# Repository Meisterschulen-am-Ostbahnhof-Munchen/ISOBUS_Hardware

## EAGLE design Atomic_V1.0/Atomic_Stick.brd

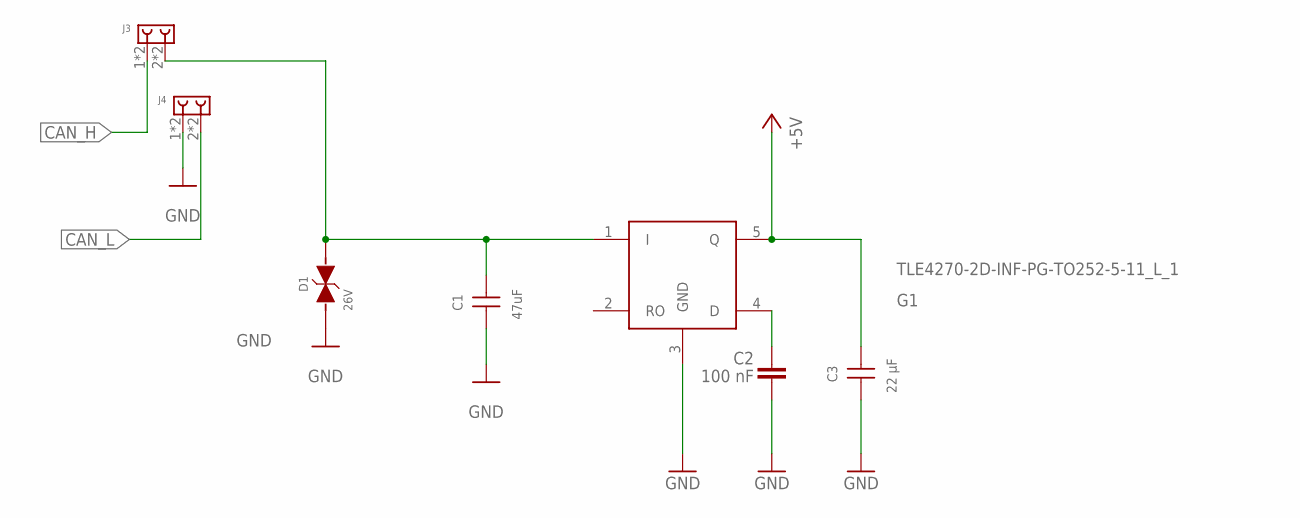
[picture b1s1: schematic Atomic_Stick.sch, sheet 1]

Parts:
C1: 47uF; WCAP-CSGP_1210_H2.5
C2: 100 nF; WCAP-CSGP_0402
C3: 22 µF; WCAP-CSGP_0805_H1.25_R
D1: 26V; WE-TVSP_DO-214AC_BIDIRECTIONAL
G1: TLE4270-2D-INF-PG-TO252-5-11_L_1; INF-PG-TO252-5-11_L_1PRIMARY
J3, J4: 695402400222

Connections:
+5V: C3.2, G1.5 (Q); also elsewhere on the board
+12V: C1.2, D1.2, G1.1 (I), J3.2, J3.A2 (2)
CAN_H: J3.1, J3.A1 (1); also elsewhere on the board
CAN_L: J4.2, J4.A2 (2); also elsewhere on the board
GND: C1.1, C2.2, C3.1, D1.1, G1.3 (GND), J4.1, J4.A1 (1); also elsewhere on the board
unnamed: C2.1, G1.4 (D)

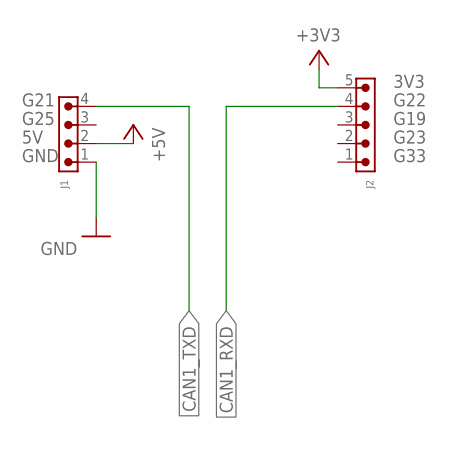
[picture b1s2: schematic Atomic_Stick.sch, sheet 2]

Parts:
J1: 6130XX11121_61300411121; 61300411121
J2: 6130XX11121_61300511121; 61300511121

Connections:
+3V3: J2.5; also elsewhere on the board
+5V: J1.2; also elsewhere on the board
CAN1_RXD: J2.4; also elsewhere on the board
CAN1_TXD: J1.4; also elsewhere on the board
GND: J1.1; also elsewhere on the board

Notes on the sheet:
GND
G25
G21
G33
G23
G19
G22
3V3

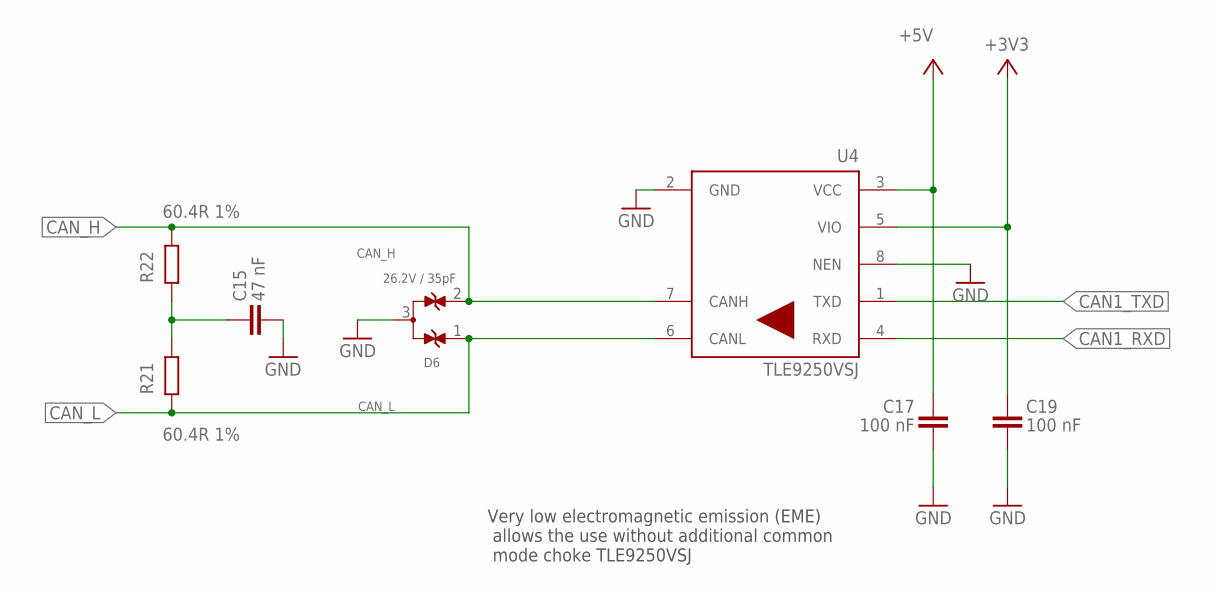
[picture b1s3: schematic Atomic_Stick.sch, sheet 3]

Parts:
C15: 47 nF; WCAP-CSGP_0402
C17, C19: 100 nF; WCAP-CSGP_0402
D6: 26.2V / 35pF; WE-TVS_SOT23-3L
R21, R22: 60.4R 1%; WCAP-CSRF_0402
U4: TLE9250VSJ; SOIC127P602X173-8N-V

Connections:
+3V3: C19.1, U4.5 (VIO); also elsewhere on the board
+5V: C17.1, U4.3 (VCC); also elsewhere on the board
CAN1_RXD: U4.4 (RXD); also elsewhere on the board
CAN1_TXD: U4.1 (TXD); also elsewhere on the board
CAN_H: D6.2, R22.2, U4.7 (CANH); also elsewhere on the board
CAN_L: D6.1, R21.1, U4.6 (CANL); also elsewhere on the board
GND: C15.2, C17.2, C19.2, D6.3, U4.2 (GND), U4.8 (NEN); also elsewhere on the board
unnamed: C15.1, R21.2, R22.1

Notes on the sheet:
Very low electromagnetic emission (EME) allows the use without additional common mode choke TLE9250VSJ

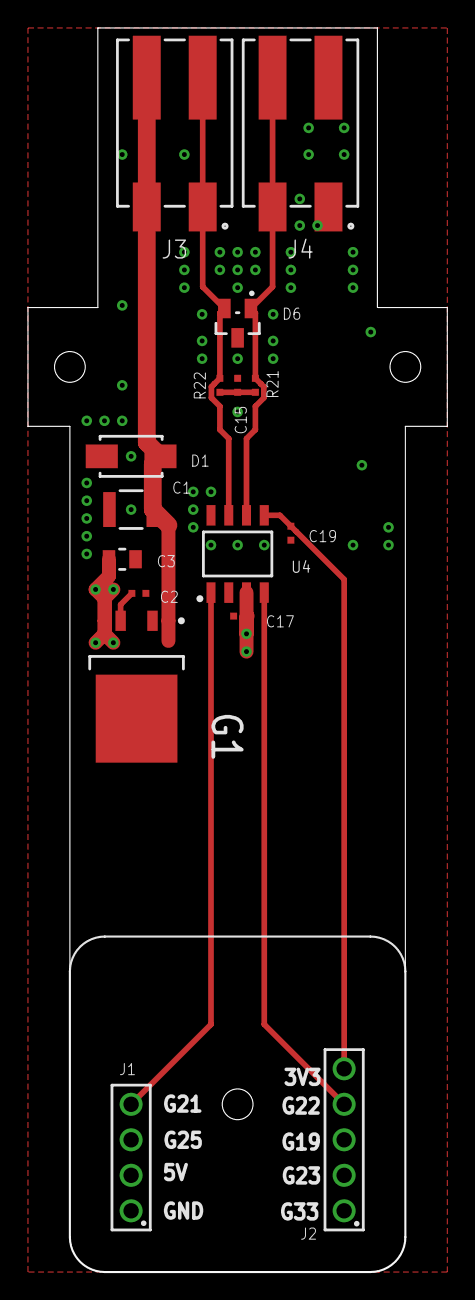
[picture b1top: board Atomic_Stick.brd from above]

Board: 2 copper layers, 30.0 x 89.0 mm, 16 parts (0 on the bottom side), 10 nets.

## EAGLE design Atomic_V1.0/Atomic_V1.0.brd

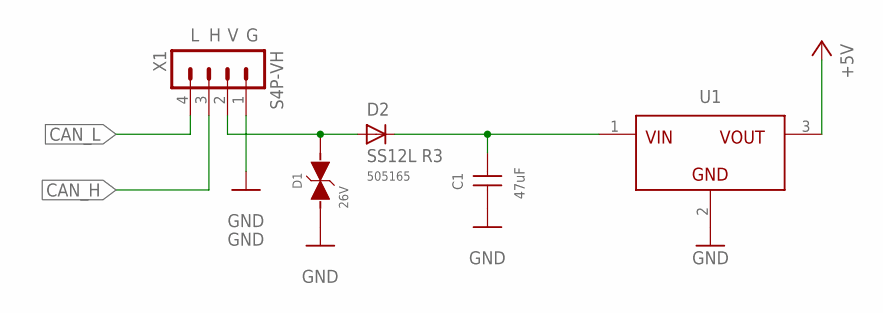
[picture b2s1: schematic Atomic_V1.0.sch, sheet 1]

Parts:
C1: 47uF; WCAP-CSGP_1210_H2.5
D1: 26V; WE-TVSP_DO-214AC_BIDIRECTIONAL
D2: SS12L R3; SMA
U1: MAGI³C-FDSM_SIP-3_173010542_173XXXX42; MAGI³C-FDSM_173XXXX42
X1: S4P-VH

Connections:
+5V: U1.3 (VOUT); also elsewhere on the board
+12V: D1.2, D2.A, X1.2; also elsewhere on the board
CAN_H: X1.3; also elsewhere on the board
CAN_L: X1.4; also elsewhere on the board
GND: C1.1, D1.1, U1.2 (GND), X1.1; also elsewhere on the board
unnamed 8: C1.2, D2.C, U1.1 (VIN); also elsewhere on the board

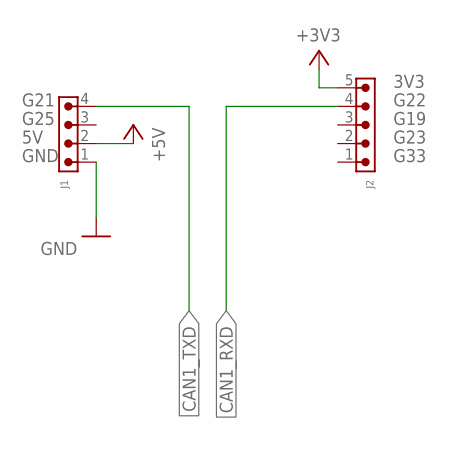
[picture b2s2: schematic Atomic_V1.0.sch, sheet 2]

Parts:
J1: 6130XX11121_61300411121; 61300411121
J2: 6130XX11121_61300511121; 61300511121

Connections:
+3V3: J2.5; also elsewhere on the board
+5V: J1.2; also elsewhere on the board
CAN1_RXD: J2.4; also elsewhere on the board
CAN1_TXD: J1.4; also elsewhere on the board
GND: J1.1; also elsewhere on the board

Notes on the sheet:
GND
G25
G21
G33
G23
G19
G22
3V3

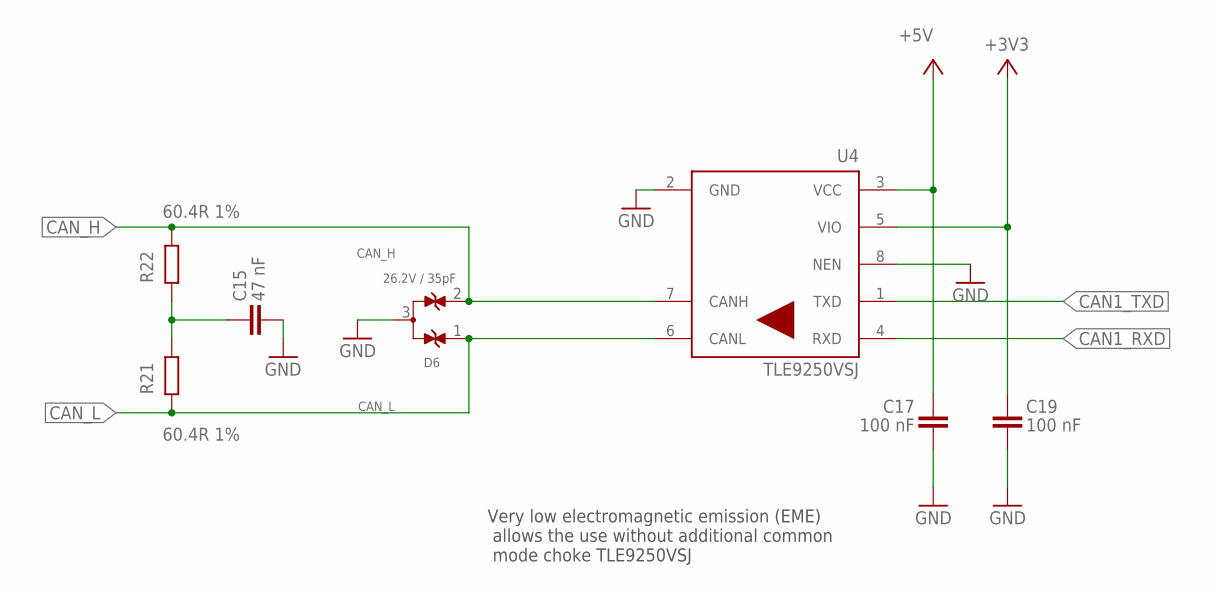
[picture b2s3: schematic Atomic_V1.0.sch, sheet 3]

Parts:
C15: 47 nF; WCAP-CSGP_0402
C17, C19: 100 nF; WCAP-CSGP_0402
D6: 26.2V / 35pF; WE-TVS_SOT23-3L
R21, R22: 60.4R 1%; WCAP-CSRF_0402
U4: TLE9250VSJ; SOIC127P602X173-8N-V

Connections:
+3V3: C19.1, U4.5 (VIO); also elsewhere on the board
+5V: C17.1, U4.3 (VCC); also elsewhere on the board
CAN1_RXD: U4.4 (RXD); also elsewhere on the board
CAN1_TXD: U4.1 (TXD); also elsewhere on the board
CAN_H: D6.2, R22.2, U4.7 (CANH); also elsewhere on the board
CAN_L: D6.1, R21.1, U4.6 (CANL); also elsewhere on the board
GND: C15.2, C17.2, C19.2, D6.3, U4.2 (GND), U4.8 (NEN); also elsewhere on the board
unnamed: C15.1, R21.2, R22.1

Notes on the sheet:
Very low electromagnetic emission (EME) allows the use without additional common mode choke TLE9250VSJ

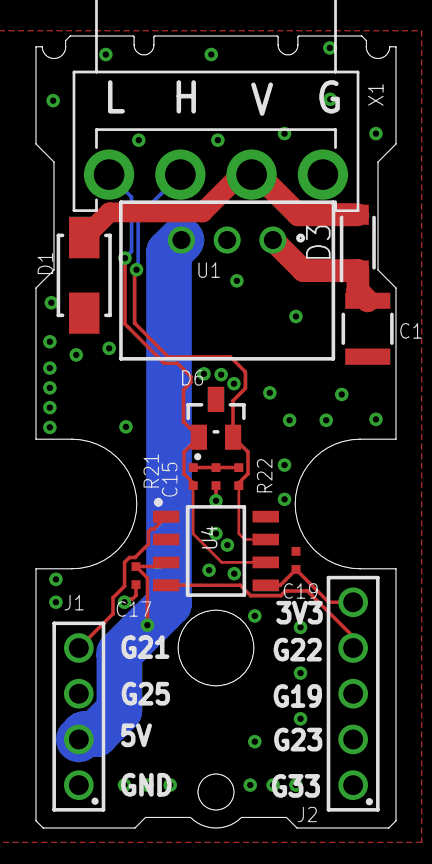
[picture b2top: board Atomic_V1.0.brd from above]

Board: 2 copper layers, 20.0 x 44.0 mm, 14 parts (0 on the bottom side), 10 nets.

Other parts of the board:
D3: SS12L_R3; SODFL3618X143N

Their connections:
+12V: D3.2; also elsewhere on the board
unnamed 8: D3.1; also elsewhere on the board

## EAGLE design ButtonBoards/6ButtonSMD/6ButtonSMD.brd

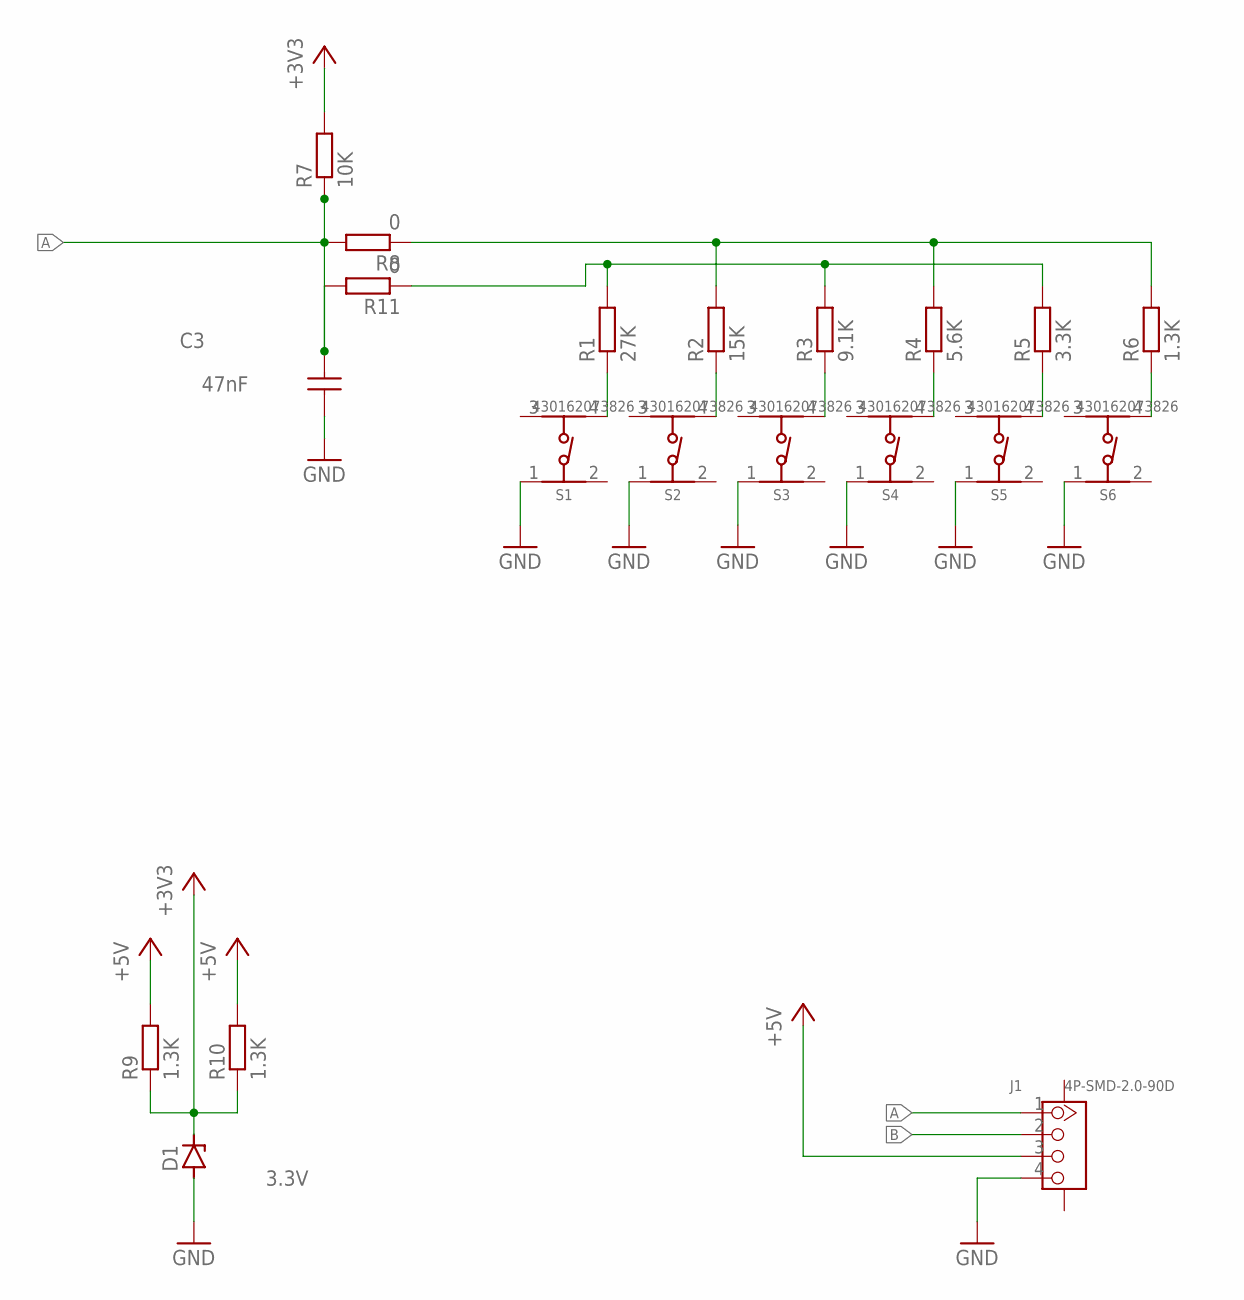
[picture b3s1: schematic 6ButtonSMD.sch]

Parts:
C3: 47nF; WCAP-CSGP_1206_H0.8
D1: 3.3V; SOD80C
J1: 4P-SMD-2.0-90D; HW4-SMD-2.0-90D
R1: 27K; R1206
R2: 15K; R1206
R3: 9.1K; R1206
R4: 5.6K; R1206
R5: 3.3K; R1206
R6, R9, R10: 1.3K; R1206
R7: 10K; R1206
R8, R11: 0; R1206
S1, S2, S3, S4, S5, S6: 430162073826

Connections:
+3V3: D1.C, R7.2, R9.1, R10.1
+5V: J1.3, R9.2, R10.2
A: C3.2, J1.1, R7.1, R8.2, R11.2
B: J1.2
GND: C3.1, D1.A, J1.4, S1.1, S2.1, S3.1, S4.1, S5.1, S6.1
unnamed: R1.1, S1.4
unnamed: R2.1, S2.4
unnamed: R3.1, S3.4
unnamed: R4.1, S4.4
unnamed: R5.1, S5.4
unnamed: R6.1, S6.4
unnamed: R2.2, R4.2, R6.2, R8.1
unnamed: R1.2, R3.2, R5.2, R11.1

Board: 2 copper layers, 20 parts (0 on the bottom side), 12 nets, no tracks yet.

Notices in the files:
parts and their libraries:
Wurth_Connectors_WR-PHD: Copyright: Würth Elektronik
